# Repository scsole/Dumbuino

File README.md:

# Dumbuino

A basic Arduino with two 10A 48V DC switches controlled using digital outputs.

## Specs

| | |
--- | ---
Microcontroller             | ATmega328P
Operating Voltage           | 5V
USB Port                    | USB 2.0 Type-C
10A 48V DC Switches         | 2 (shared with digital pins 9 & 10)
Digital I/O Pins            | 14 (of which 6 provide PWM output)
PWM Digital I/O Pins        | 6
Analog Input Pins           | 6
DC Current per I/O Pin      | 20 mA
DC Current for 3.3V Pin     | 50 mA
Flash Memory                | 32 KB (ATmega328P) of which 0.5 KB used by bootloader
SRAM                        | 2 KB (ATmega328P)
EEPROM                      | 1 KB (ATmega328P)
Clock Speed                 | 16 MHz
LED_BUILTIN                 | 13

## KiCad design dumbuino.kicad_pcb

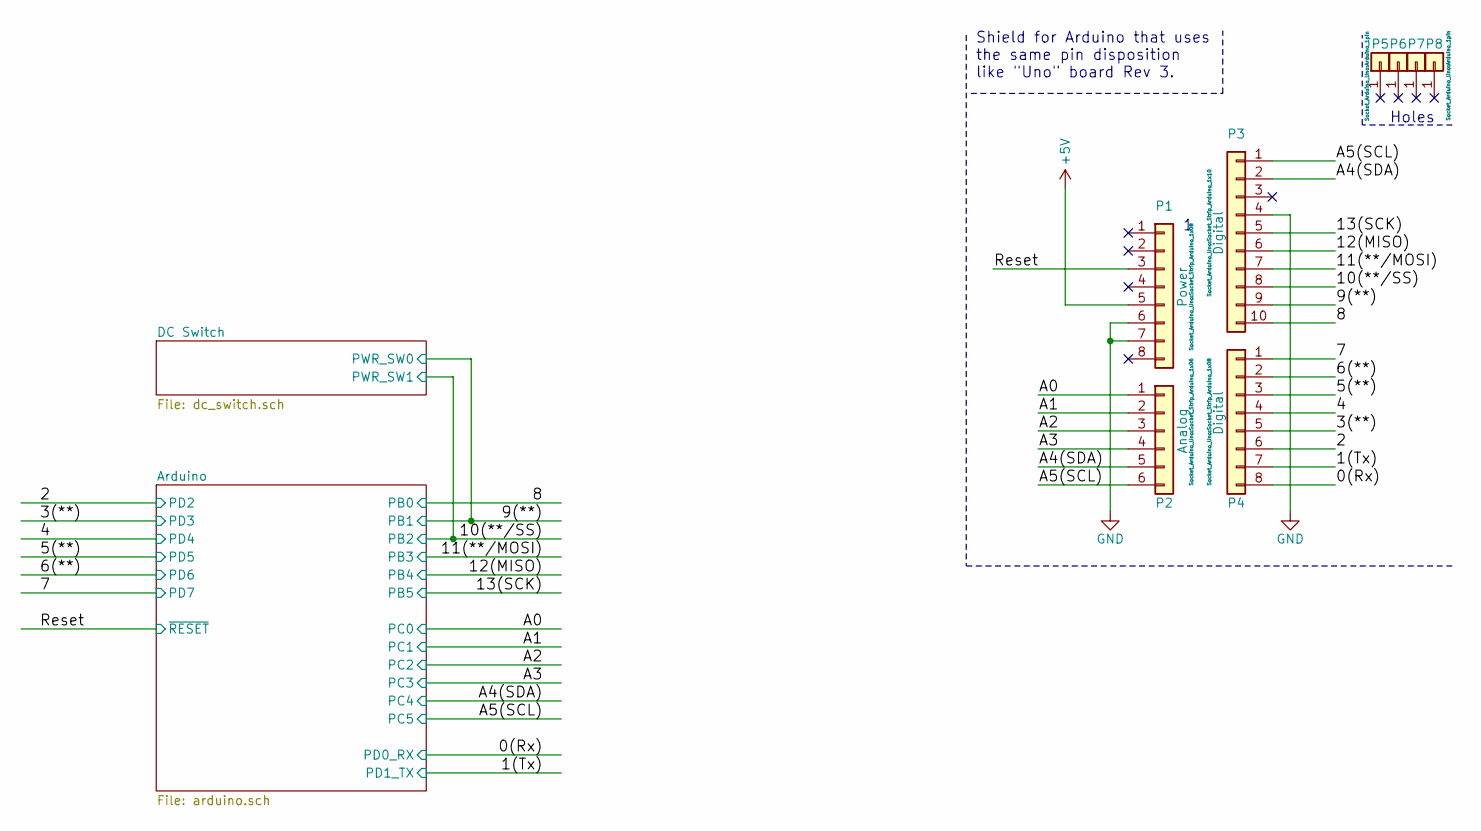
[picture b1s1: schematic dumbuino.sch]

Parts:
P1: Power; Socket_Strip_Arduino_1x08
P2: Analog; Socket_Strip_Arduino_1x06
P3: Digital; Socket_Strip_Arduino_1x10
P4: Digital; Socket_Strip_Arduino_1x08
P5, P6, P7, P8: CONN_01X01; Arduino_1pin

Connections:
+5V: P1.5; also elsewhere on the board
/0(Rx): P4.8; also elsewhere on the board
/1(Tx): P4.7; also elsewhere on the board
/2: P4.6; also elsewhere on the board
/3(**): P4.5; also elsewhere on the board
/4: P4.4; also elsewhere on the board
/5(**): P4.3; also elsewhere on the board
/6(**): P4.2; also elsewhere on the board
/7: P4.1; also elsewhere on the board
/8: P3.10; also elsewhere on the board
/9(**): P3.9; also elsewhere on the board
/10(**/SS): P3.8; also elsewhere on the board
/11(**/MOSI): P3.7; also elsewhere on the board
/12(MISO): P3.6; also elsewhere on the board
/13(SCK): P3.5; also elsewhere on the board
/A0: P2.1; also elsewhere on the board
/A1: P2.2; also elsewhere on the board
/A2: P2.3; also elsewhere on the board
/A3: P2.4; also elsewhere on the board
/A4(SDA): P2.5, P3.2; also elsewhere on the board
/A5(SCL): P2.6, P3.1; also elsewhere on the board
/Reset: P1.3; also elsewhere on the board
GND: P1.6, P1.7, P3.4; also elsewhere on the board

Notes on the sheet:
Holes
Shield for Arduino that uses the same pin disposition like "Uno" board Rev 3.

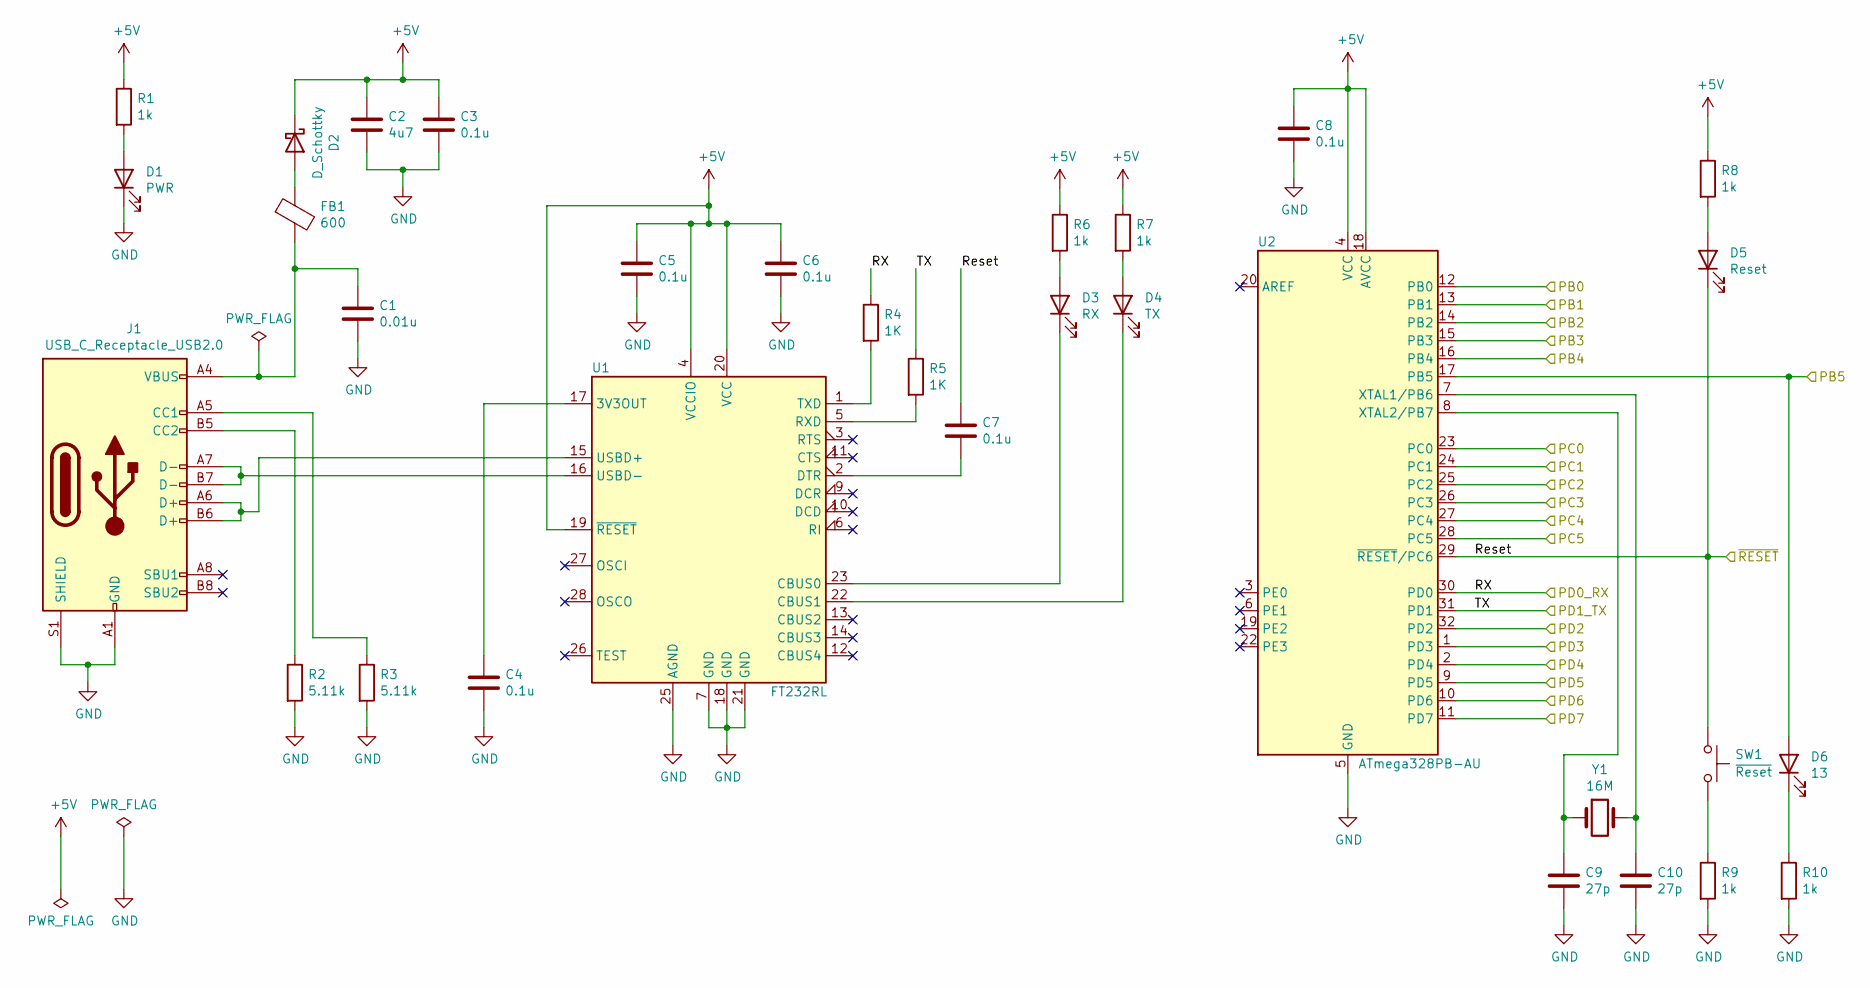
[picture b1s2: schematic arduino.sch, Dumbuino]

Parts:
C1: 0.01u; C_0805_2012Metric_Pad1.15x1.40mm_HandSolder
C2: 4u7; C_0805_2012Metric_Pad1.15x1.40mm_HandSolder
C3, C4, C5, C6, C7, C8: 0.1u; C_0805_2012Metric_Pad1.15x1.40mm_HandSolder
C9, C10: 27p; C_0805_2012Metric_Pad1.15x1.40mm_HandSolder
D1: PWR; LED_0805_2012Metric_Pad1.15x1.40mm_HandSolder
D2: D_Schottky; D_SOD-123F
D3: RX; LED_0805_2012Metric_Pad1.15x1.40mm_HandSolder
D4: TX; LED_0805_2012Metric_Pad1.15x1.40mm_HandSolder
D5: Reset; LED_0805_2012Metric_Pad1.15x1.40mm_HandSolder
D6: 13; LED_0805_2012Metric_Pad1.15x1.40mm_HandSolder
FB1: 600; L_0805_2012Metric_Pad1.15x1.40mm_HandSolder
J1: USB_C_Receptacle_USB2.0; USB_C_Receptacle_HRO_TYPE-C-31-M-12
R1, R6, R7, R8, R9, R10: 1k; R_0805_2012Metric_Pad1.15x1.40mm_HandSolder
R2, R3: 5.11k; R_0805_2012Metric_Pad1.15x1.40mm_HandSolder
R4, R5: 1K; R_0805_2012Metric_Pad1.15x1.40mm_HandSolder
SW1: ~Reset; SW_SPST_PTS645
U1: FT232RL; SSOP-28_5.3x10.2mm_P0.65mm
U2: ATmega328PB-AU; TQFP-32_7x7mm_P0.8mm
Y1: 16M; Crystal_HC49-U_Vertical

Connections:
+5V: C2.1, C3.1, C5.1, C6.1, C8.1, D2.1 (K), R1.1, R6.1, R7.1, R8.1, U1.4 (VCCIO), U1.19 (~RESET~), U1.20 (VCC), U2.4 (VCC), U2.18 (AVCC); also elsewhere on the board
/0(Rx): R4.1, U2.30 (PD0); also elsewhere on the board
/1(Tx): R5.1, U2.31 (PD1); also elsewhere on the board
/2: U2.32 (PD2); also elsewhere on the board
/3(**): U2.1 (PD3); also elsewhere on the board
/4: U2.2 (PD4); also elsewhere on the board
/5(**): U2.9 (PD5); also elsewhere on the board
/6(**): U2.10 (PD6); also elsewhere on the board
/7: U2.11 (PD7); also elsewhere on the board
/8: U2.12 (PB0); also elsewhere on the board
/9(**): U2.13 (PB1); also elsewhere on the board
/10(**/SS): U2.14 (PB2); also elsewhere on the board
/11(**/MOSI): U2.15 (PB3); also elsewhere on the board
/12(MISO): U2.16 (PB4); also elsewhere on the board
/13(SCK): D6.2 (A), U2.17 (PB5); also elsewhere on the board
/A0: U2.23 (PC0); also elsewhere on the board
/A1: U2.24 (PC1); also elsewhere on the board
/A2: U2.25 (PC2); also elsewhere on the board
/A3: U2.26 (PC3); also elsewhere on the board
/A4(SDA): U2.27 (PC4); also elsewhere on the board
/A5(SCL): U2.28 (PC5); also elsewhere on the board
/Reset: C7.2, D5.1 (K), SW1.1, U2.29 (~RESET~/PC6); also elsewhere on the board
GND: C1.2, C2.2, C3.2, C4.2, C5.2, C6.2, C8.2, C9.2, C10.2, D1.1 (K), J1.A1 (GND), J1.A12 (GND), J1.B1 (GND), J1.B12 (GND), J1.S1 (SHIELD), R2.2, R3.2, R9.2, R10.2, U1.7 (GND), U1.18 (GND), U1.21 (GND), U1.25 (AGND), U2.5 (GND), U2.21 (GND); also elsewhere on the board
unnamed: C1.1, FB1.2, J1.A4 (VBUS), J1.A9 (VBUS), J1.B4 (VBUS), J1.B9 (VBUS)
unnamed: C4.1, U1.17 (3V3OUT)
unnamed: C7.1, U1.2 (DTR)
unnamed: C9.1, U2.8 (XTAL2/PB7), Y1.1
unnamed: C10.1, U2.7 (XTAL1/PB6), Y1.2
unnamed: D1.2 (A), R1.2
unnamed: D2.2 (A), FB1.1
unnamed: D3.1 (K), U1.23 (CBUS0)
unnamed: D3.2 (A), R6.2
unnamed: D4.1 (K), U1.22 (CBUS1)
unnamed: D4.2 (A), R7.2
unnamed: D5.2 (A), R8.2
unnamed: D6.1 (K), R10.1
unnamed: J1.A5 (CC1), R3.1
unnamed: J1.A6 (D+), J1.B6 (D+), U1.15 (USBD+)
unnamed: J1.A7 (D-), J1.B7 (D-), U1.16 (USBD-)
unnamed: J1.B5 (CC2), R2.1
unnamed: R4.2, U1.1 (TXD)
unnamed: R5.2, U1.5 (RXD)
unnamed: R9.1, SW1.2

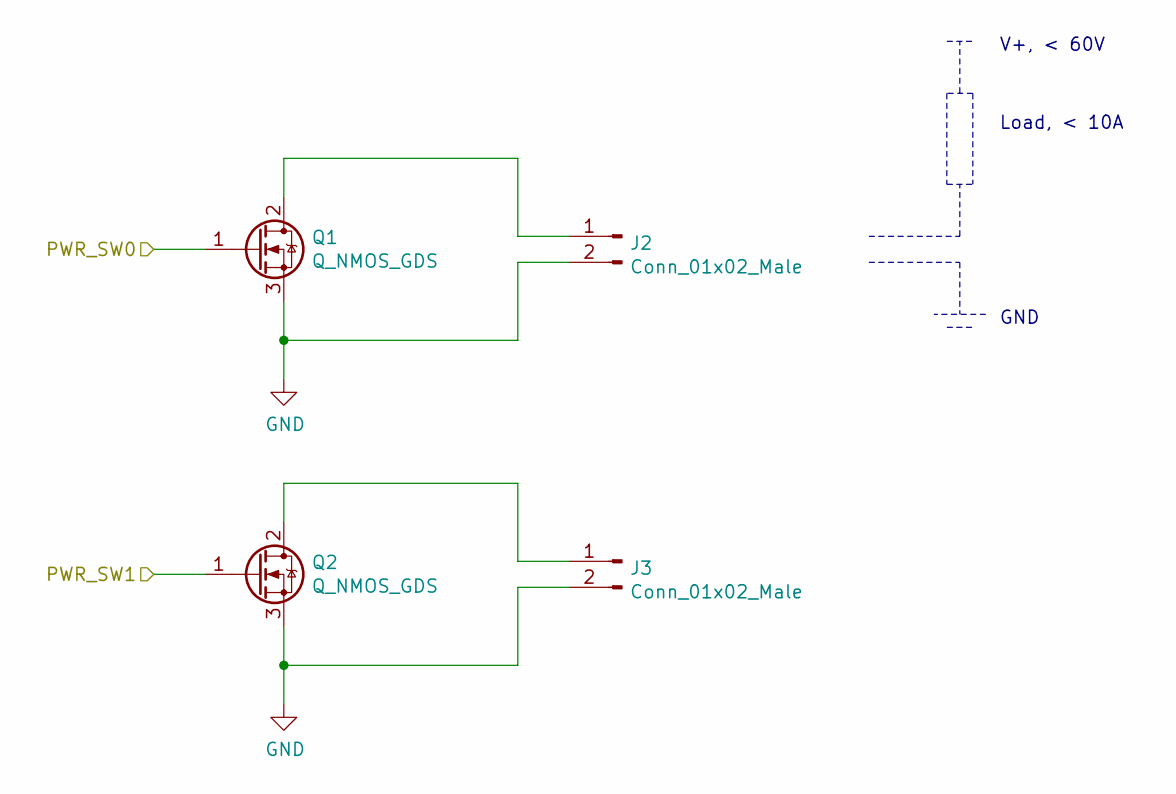
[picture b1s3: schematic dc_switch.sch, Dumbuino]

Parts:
J2, J3: Conn_01x02_Male; PhoenixContact_MSTBVA_2,5_2-G-5,08_1x02_P5.08mm_Vertical
Q1, Q2: Q_NMOS_GDS; TO-220F-3_Vertical

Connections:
/9(**): Q1.1 (G); also elsewhere on the board
/10(**/SS): Q2.1 (G); also elsewhere on the board
GND: J2.2, J3.2, Q1.3 (S), Q2.3 (S); also elsewhere on the board
unnamed: J2.1, Q1.2 (D)
unnamed: J3.1, Q2.2 (D)

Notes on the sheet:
GND
Load, < 10A
V+, < 60V

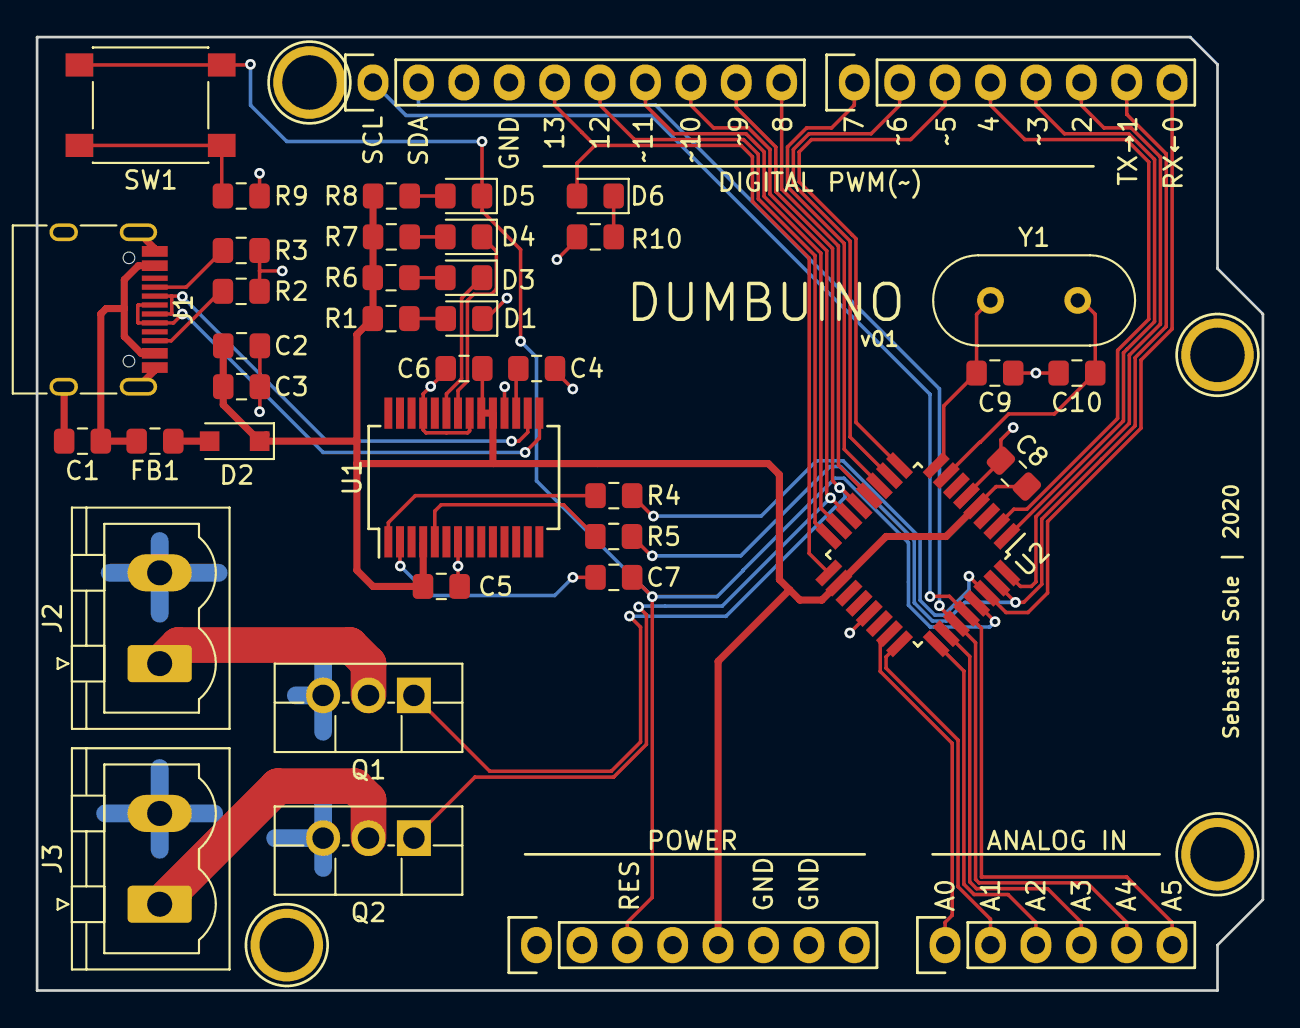
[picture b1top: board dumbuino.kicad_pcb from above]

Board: 4 copper layers, 68.6 x 53.3 mm, 44 parts (0 on the bottom side), 45 nets.

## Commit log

2020-09-20 Initial template files
2020-09-20 Added arduino schematic
2020-09-20 Added two 48V digital outputs
2020-09-20 Associated footprints
2020-09-20 Defined board properties
2020-09-20 Initial component placement
2020-09-20 Finished initial board layout
2020-09-20 Adjusted tracks
2020-09-20 Updated F.SilkS
2020-09-23 Update track width
2020-09-23 Generated gerbers
2020-10-14 Updated values
2020-11-06 Added README.md
2020-11-06 Added specs
